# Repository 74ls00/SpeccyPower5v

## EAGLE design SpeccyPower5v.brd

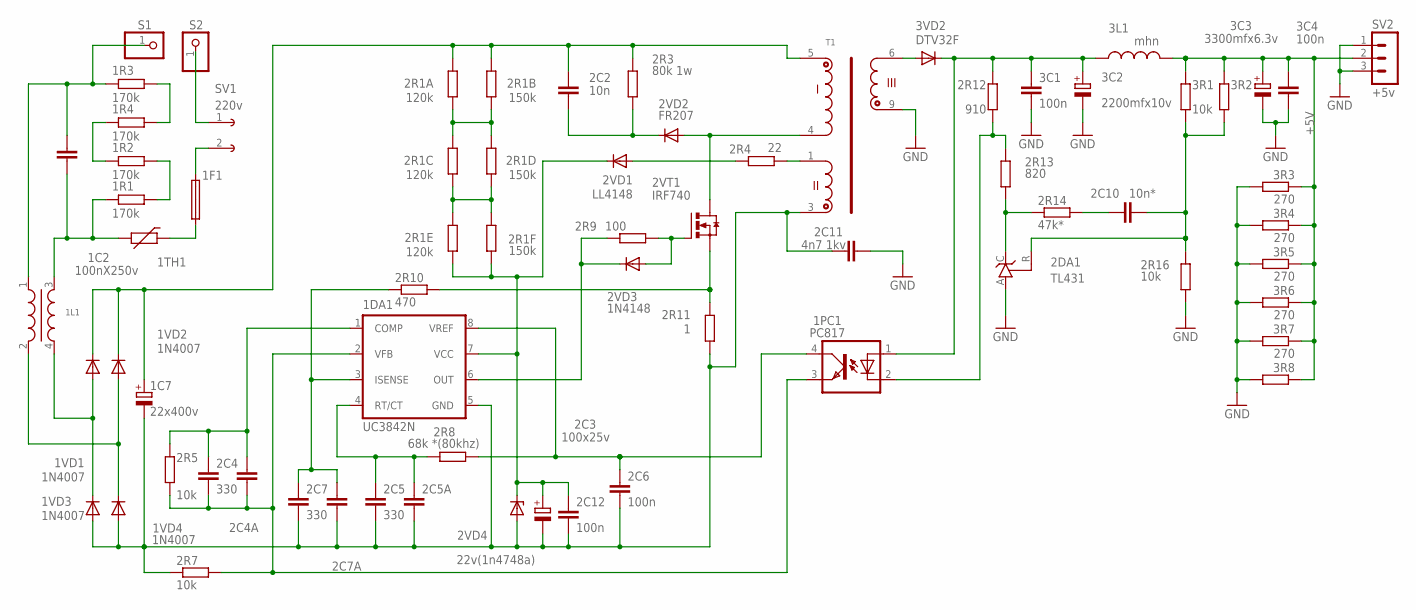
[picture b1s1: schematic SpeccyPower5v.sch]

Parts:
1C2: 100nX250v; C150-064X183
1C7: 22x400v; TT5D11L
1DA1: UC3842N; DIL08
1F1: SHK20L
1L1: LFLF-10X13; LF-10X13
1PC1: PC817; DIL04
1R1, 1R2, 1R3, 1R4: 170k; R0805
1TH1: THERMISTOR-7,5; R-7,5
1VD1, 1VD2, 1VD3, 1VD4: 1N4007; DO41-10
2C2: 10n; C102-043X133
2C3: 100x25v; E2,5-6
2C4, 2C5, 2C7: 330; C050-025X075
2C4A, 2C5A, 2C7A: C-EUC0805; C0805
2C6, 2C12, 3C1, 3C4: 100n; C0805
2C10: 10n*; C050-025X075
2C11: 4n7 1kv; C075-032X103
2DA1: TL431; TO92-CLP
2R1A, 2R1C, 2R1E: 120k; M0805
2R1B, 2R1D, 2R1F: 150k; M0805
2R3: 80k 1w; P0613/15
2R4: 22; M0805
2R5, 2R7: 10k; 0207/10
2R8: 68k *(80khz); R0805
2R9: 100; 0204/7
2R10: 470; 0207/10
2R11: 1; 0411/15
2R12: 910; R0805
2R13: 820; 0204/7
2R14: 47k*; R0805
2R16, 3R1: 10k; R0805
2VD1: LL4148; SOD80C
2VD2: FR207; DO35-10
2VD3: 1N4148; DO35-7
2VD4: 22v(1n4748a); DO35Z10
2VT1: IRF740; TO262-V
3C2: 2200mfx10v; TT2D7L
3C3: 3300mfx6.3v; TT2D7L-2
3L1: mhn; LAL02
3R2, 3R8: R-EU_R0805; R0805
3R3, 3R4, 3R5, 3R6, 3R7: 270; R0805
3VD2: DTV32F; DO220S
S1, S2: PINHD-1X1; 1X01
SV1: 220v; IEC320-C8
SV2: +5v; MA03-1
T1: TRANS_ER29; ER29

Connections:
817-3: 1DA1.2 (VFB), 1PC1.3 (EMIT), 2C4.2, 2C4A.2, 2R5.1, 2R7.2
+5V: 3C3.+, 3C4.1, 3L1.2, 3R1.2, 3R2.2, 3R3.1, 3R4.1, 3R5.1, 3R6.1, 3R7.1, 3R8.1, SV2.2
+16IN: 1DA1.7 (VCC), 2C3.+, 2C12.1, 2R1E.1, 2R1F.2, 2VD1.C, 2VD4.C
+IN: 1C7.+, 1VD1.C, 1VD2.C, 2C2.1, 2R1A.2, 2R1B.2, 2R3.2, T1.5 (IN2)
-IN: 1C7.-, 1DA1.5 (GND), 1VD3.A, 1VD4.A, 2C3.-, 2C5.2, 2C5A.2, 2C6.2, 2C7.2, 2C7A.2, 2C11.1, 2C12.2, 2R7.1, 2R11.1, 2VD4.A, T1.3 (OP2)
COMP: 1DA1.1 (COMP), 2C4.1, 2C4A.1, 2R5.2
GND: 2C11.2, 2DA1.A, 2R16.1, 3C1.2, 3C2.-, 3C3.-, 3C4.2, 3R3.2, 3R4.2, 3R5.2, 3R6.2, 3R7.2, 3R8.2, SV2.1, SV2.3, T1.9 (5V2)
unnamed: 1L1.4, 1VD1.A, 1VD3.C
unnamed: 1C2.1, 1L1.3, 1R1.1, 1TH1.2
unnamed: 1DA1.4 (RT/CT), 2C5.1, 2C5A.1, 2R8.1
unnamed: 1DA1.3 (ISENSE), 2C7.1, 2C7A.1, 2R10.1
unnamed: 2R4.1, 2VD1.A
unnamed: 1DA1.6 (OUT), 2R9.1, 2VD3.C
unnamed: 2R9.2, 2VD3.A, 2VT1.1 (G)
unnamed: 1PC1.2 (C), 2R12.1, 2R13.2
unnamed: 1PC1.1 (A), 2R12.2, 3C1.1, 3C2.+, 3L1.1, 3VD2.C
unnamed: 2DA1.C, 2R13.1, 2R14.1
unnamed: 1F1.1A, SV1.2
unnamed: 2C10.2, 2R14.2
unnamed: 2VD2.A, 2VT1.2 (D), T1.4 (IN1)
unnamed: 1R3.2, 1R4.2
unnamed: 2R1C.1, 2R1D.1, 2R1E.2, 2R1F.1
unnamed: 1DA1.8 (VREF), 1PC1.4 (COL), 2C6.1, 2R8.2
unnamed: 2R10.2, 2R11.2, 2VT1.3 (S)
unnamed: 2R4.2, T1.1 (OP1)
unnamed: 1R2.1, 1R4.1
unnamed: 2C10.1, 2DA1.R, 2R16.2, 3R1.1, 3R2.1
unnamed: 3VD2.A, T1.6 (5V1)
unnamed: 2R1A.1, 2R1B.1, 2R1C.2, 2R1D.2
unnamed: 2C2.2, 2R3.1, 2VD2.C
unnamed: 1C2.2, 1L1.1, 1R3.1, S1.1
unnamed: S2.1, SV1.1
unnamed: 1L1.2, 1VD2.A, 1VD4.C
unnamed: 1F1.2A, 1TH1.1
unnamed: 1R1.2, 1R2.2

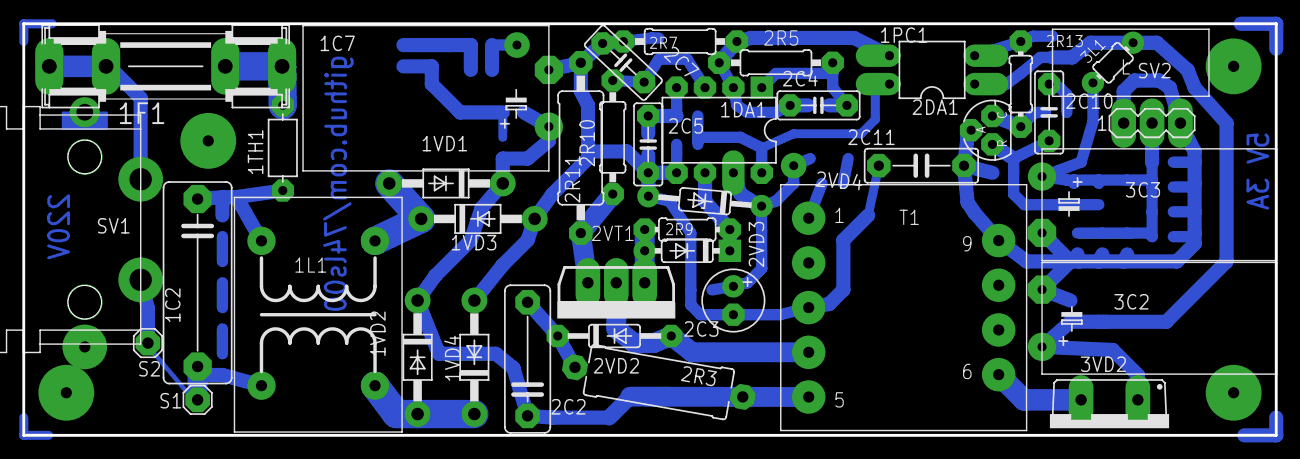
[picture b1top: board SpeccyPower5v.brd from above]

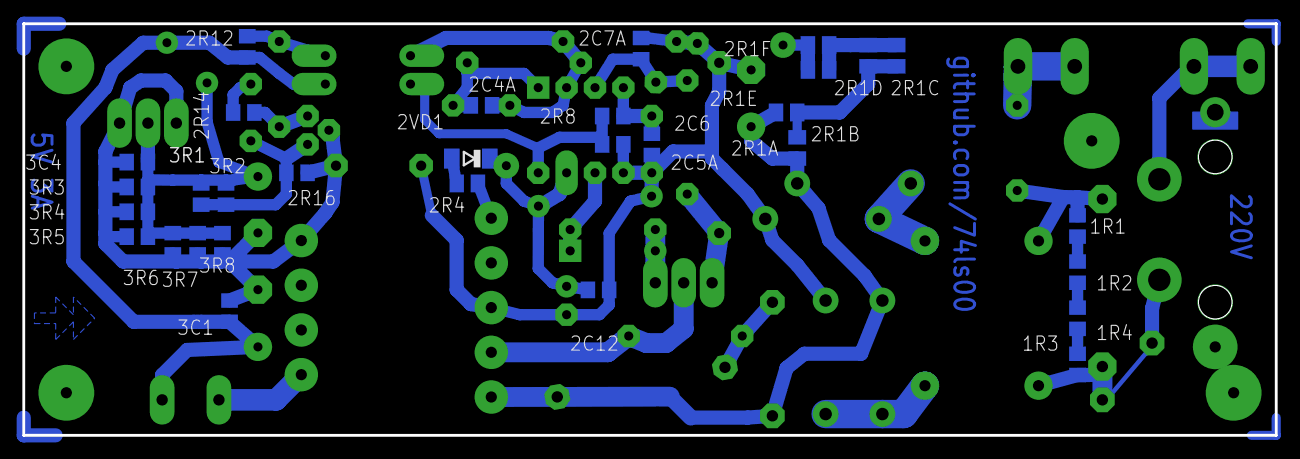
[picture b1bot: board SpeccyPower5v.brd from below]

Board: 2 copper layers, 112.1 x 36.8 mm, 71 parts (31 on the bottom side), 35 nets.

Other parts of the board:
U$1: _L

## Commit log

2017-10-31 test v h
